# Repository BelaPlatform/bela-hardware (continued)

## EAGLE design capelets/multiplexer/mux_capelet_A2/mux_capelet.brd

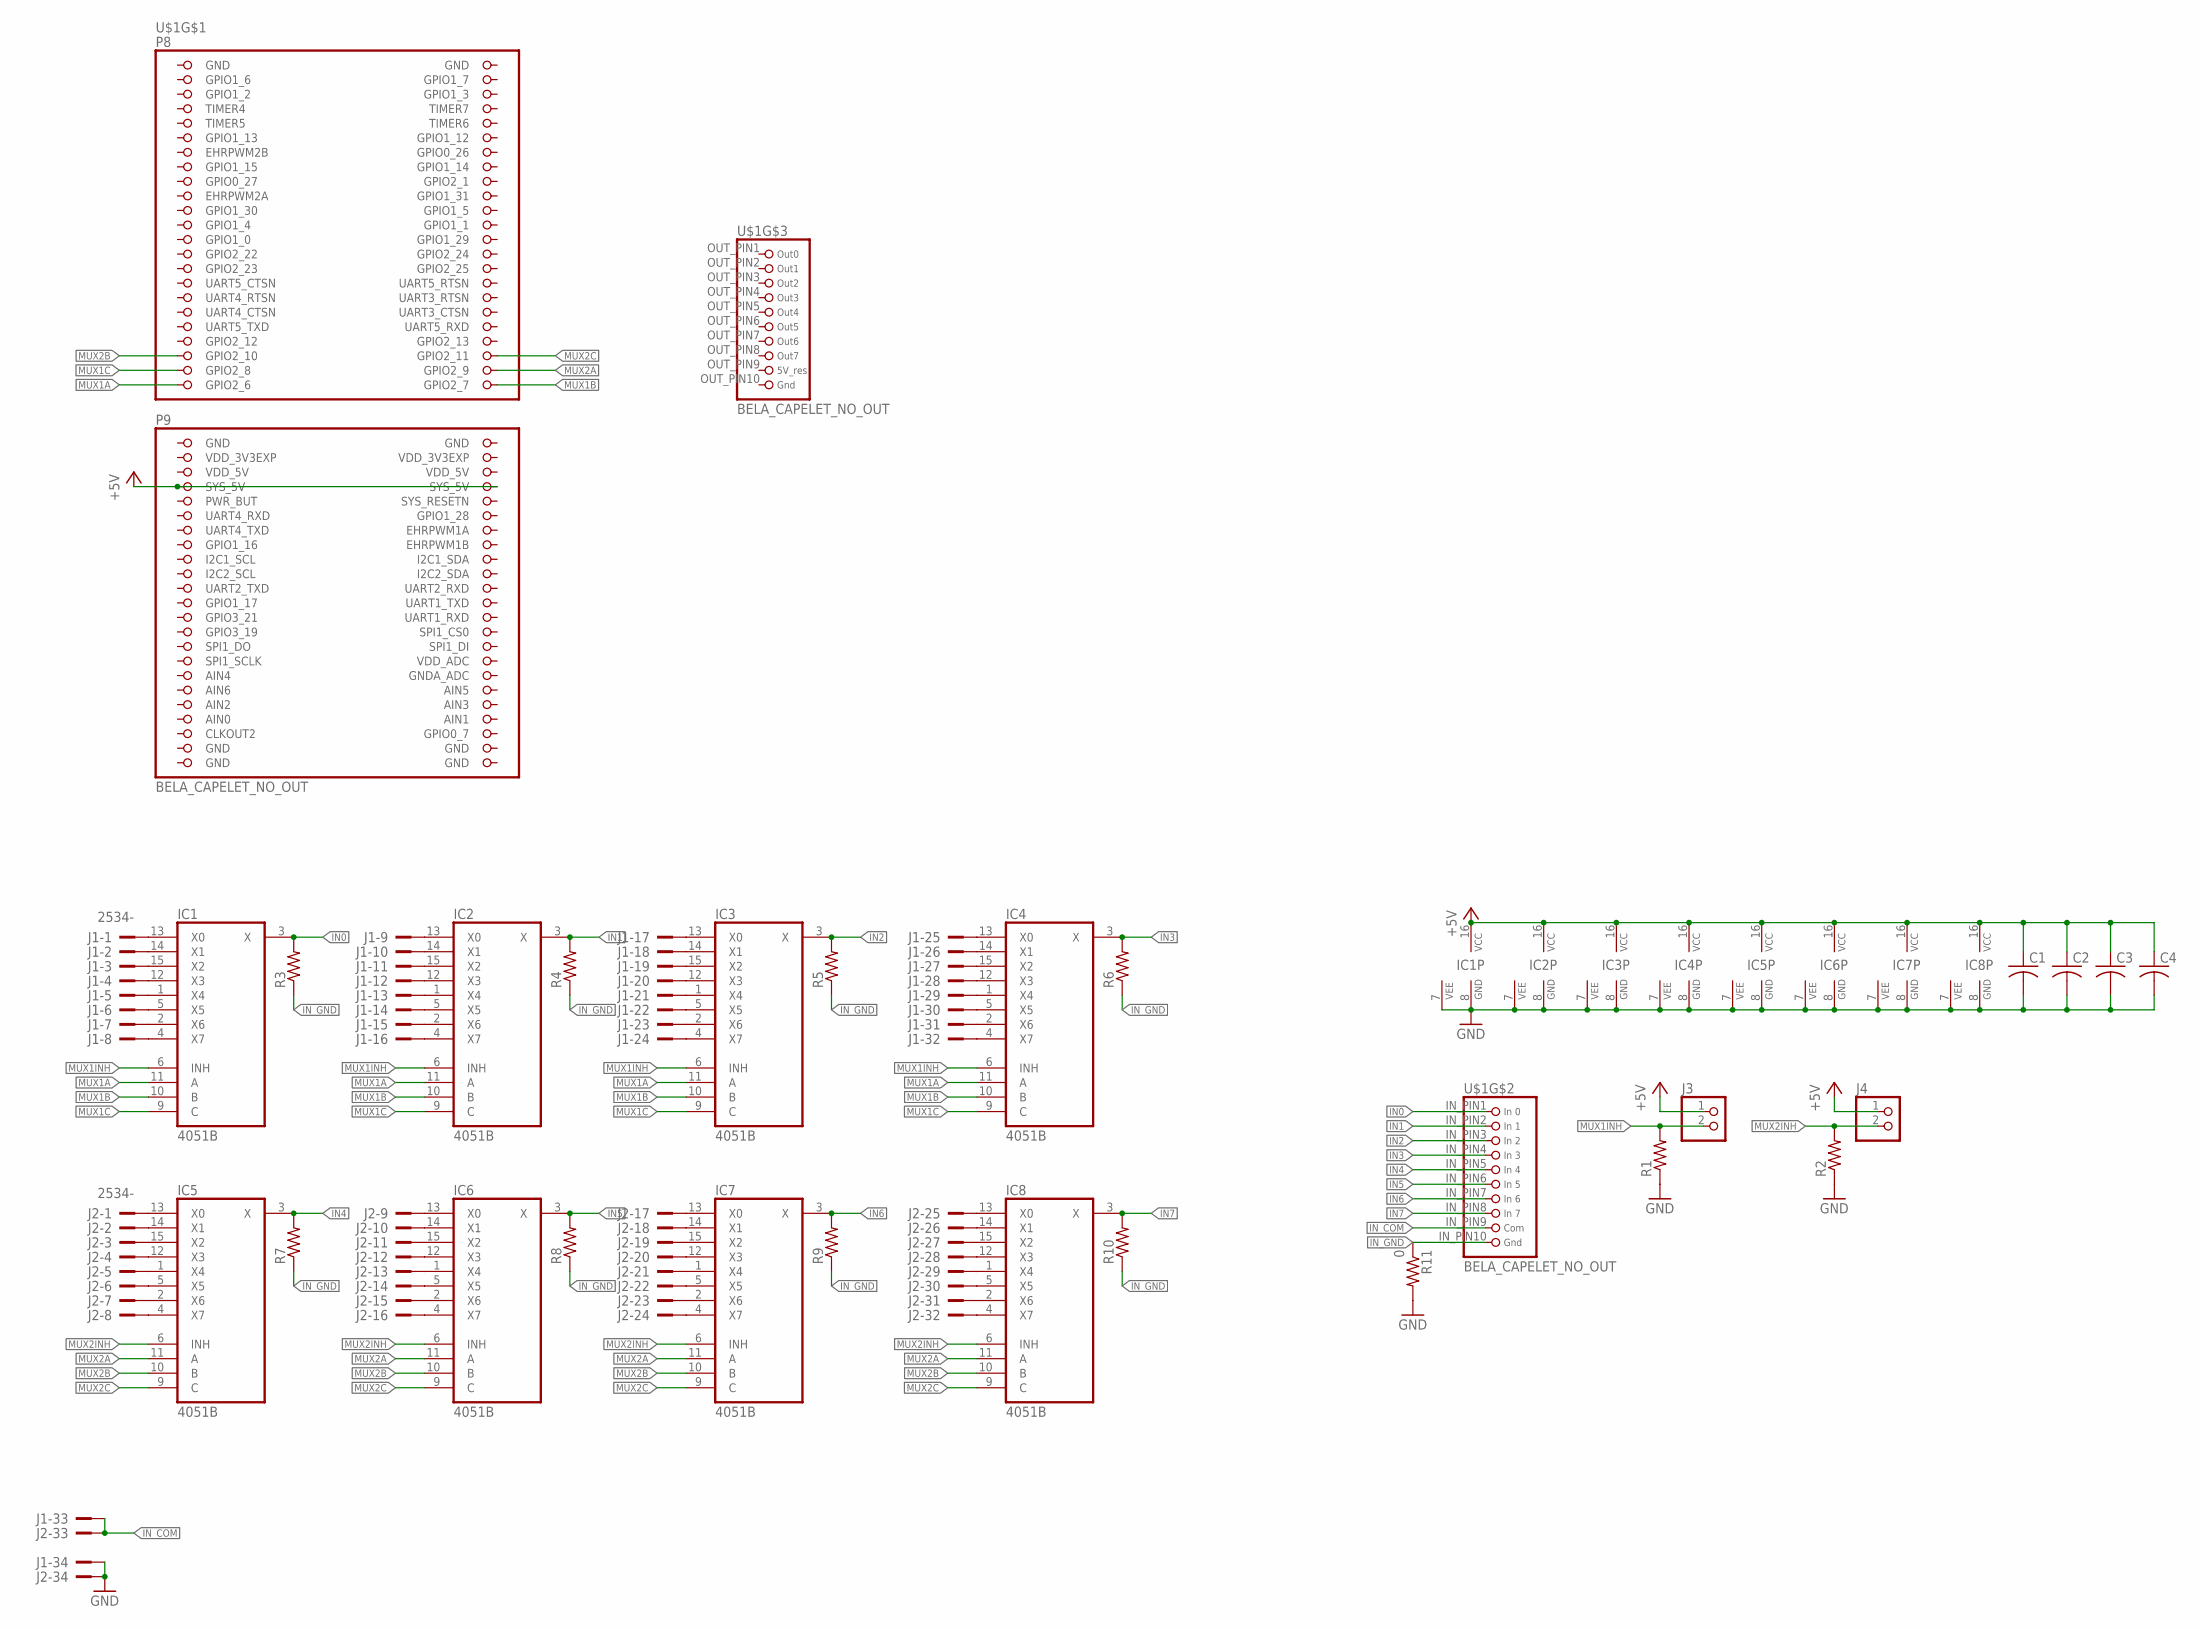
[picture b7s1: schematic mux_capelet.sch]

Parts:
C1, C2, C3, C4: C-USC0603; C0603
IC1, IC2, IC3, IC4, IC5, IC6, IC7, IC8: 4051B; TSSOP16-PW
J1, J2: 2534-; PAK100/2500-34
J3, J4: PINHD-1X2; 1X02
R1, R2, R3, R4, R5, R6, R7, R8, R9, R10: R-US_R0603; R0603
R11: 0; R0603
U$1: BELA_CAPELET_NO_OUT; BELA_CAPELET_NO_OUTLINE

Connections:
+5V: C1.1, C2.1, C3.1, C4.1, IC1.16 (VCC), IC2.16 (VCC), IC3.16 (VCC), IC4.16 (VCC), IC5.16 (VCC), IC6.16 (VCC), IC7.16 (VCC), IC8.16 (VCC), J3.1, J4.1, U$1.53 (SYS_5V), U$1.54 (SYS_5V)
AIN0: U$1.85 (AIN0)
GND: C1.2, C2.2, C3.2, C4.2, IC1.7 (VEE), IC1.8 (GND), IC2.7 (VEE), IC2.8 (GND), IC3.7 (VEE), IC3.8 (GND), IC4.7 (VEE), IC4.8 (GND), IC5.7 (VEE), IC5.8 (GND), IC6.7 (VEE), IC6.8 (GND), IC7.7 (VEE), IC7.8 (GND), IC8.7 (VEE), IC8.8 (GND), J1.34, J2.34, R1.1, R2.1, R11.2, U$1.1 (GND), U$1.2 (GND), U$1.47 (GND), U$1.48 (GND), U$1.89 (GND), U$1.90 (GND), U$1.91 (GND), U$1.92 (GND)
IN0: IC1.3 (X), R3.2, U$1.IN_PIN1 (1)
IN1: IC2.3 (X), R4.2, U$1.IN_PIN2 (2)
IN2: IC3.3 (X), R5.2, U$1.IN_PIN3 (3)
IN3: IC4.3 (X), R6.2, U$1.IN_PIN4 (4)
IN4: IC5.3 (X), R7.2, U$1.IN_PIN5 (5)
IN5: IC6.3 (X), R8.2, U$1.IN_PIN6 (6)
IN6: IC7.3 (X), R9.2, U$1.IN_PIN7 (7)
IN7: IC8.3 (X), R10.2, U$1.IN_PIN8 (8)
IN_COM: J1.33, J2.33, U$1.IN_PIN9 (9)
IN_GND: R3.1, R4.1, R5.1, R6.1, R7.1, R8.1, R9.1, R10.1, R11.1, U$1.IN_PIN10 (10)
J2: IC7.15 (X2), J2.19
MUX1A: IC1.11 (A), IC2.11 (A), IC3.11 (A), IC4.11 (A), U$1.45 (GPIO2_6)
MUX1B: IC1.10 (B), IC2.10 (B), IC3.10 (B), IC4.10 (B), U$1.46 (GPIO2_7)
MUX1C: IC1.9 (C), IC2.9 (C), IC3.9 (C), IC4.9 (C), U$1.43 (GPIO2_8)
MUX1INH: IC1.6 (INH), IC2.6 (INH), IC3.6 (INH), IC4.6 (INH), J3.2, R1.2
MUX2A: IC5.11 (A), IC6.11 (A), IC7.11 (A), IC8.11 (A), U$1.44 (GPIO2_9)
MUX2B: IC5.10 (B), IC6.10 (B), IC7.10 (B), IC8.10 (B), U$1.41 (GPIO2_10)
MUX2C: IC5.9 (C), IC6.9 (C), IC7.9 (C), IC8.9 (C), U$1.42 (GPIO2_11)
MUX2INH: IC5.6 (INH), IC6.6 (INH), IC7.6 (INH), IC8.6 (INH), J4.2, R2.2
unnamed: IC6.13 (X0), J2.9
unnamed: IC6.14 (X1), J2.10
unnamed: IC6.15 (X2), J2.11
unnamed: IC6.12 (X3), J2.12
unnamed: IC6.1 (X4), J2.13
unnamed: IC6.5 (X5), J2.14
unnamed: IC6.2 (X6), J2.15
unnamed: IC6.4 (X7), J2.16
unnamed: IC5.13 (X0), J2.1
unnamed: IC5.14 (X1), J2.2
unnamed: IC5.15 (X2), J2.3
unnamed: IC5.12 (X3), J2.4
unnamed: IC5.1 (X4), J2.5
unnamed: IC5.5 (X5), J2.6
unnamed: IC5.2 (X6), J2.7
unnamed: IC5.4 (X7), J2.8
unnamed: IC7.13 (X0), J2.17
unnamed: IC7.14 (X1), J2.18
unnamed: IC7.12 (X3), J2.20
unnamed: IC7.1 (X4), J2.21
unnamed: IC7.5 (X5), J2.22
unnamed: IC7.2 (X6), J2.23
unnamed: IC7.4 (X7), J2.24
unnamed: IC8.13 (X0), J2.25
unnamed: IC8.14 (X1), J2.26
unnamed: IC8.15 (X2), J2.27
unnamed: IC8.12 (X3), J2.28
unnamed: IC8.1 (X4), J2.29
unnamed: IC8.5 (X5), J2.30
unnamed: IC8.2 (X6), J2.31
unnamed: IC8.4 (X7), J2.32
unnamed: IC1.13 (X0), J1.1
unnamed: IC1.14 (X1), J1.2
unnamed: IC1.15 (X2), J1.3
unnamed: IC1.12 (X3), J1.4
unnamed: IC1.1 (X4), J1.5
unnamed: IC1.5 (X5), J1.6
unnamed: IC1.2 (X6), J1.7
unnamed: IC1.4 (X7), J1.8
unnamed: IC2.13 (X0), J1.9
unnamed: IC2.14 (X1), J1.10
unnamed: IC2.15 (X2), J1.11
unnamed: IC2.12 (X3), J1.12
unnamed: IC2.1 (X4), J1.13
unnamed: IC2.5 (X5), J1.14
unnamed: IC2.2 (X6), J1.15
unnamed: IC2.4 (X7), J1.16
unnamed: IC3.13 (X0), J1.17
unnamed: IC3.14 (X1), J1.18
unnamed: IC3.15 (X2), J1.19
unnamed: IC3.12 (X3), J1.20
unnamed: IC3.1 (X4), J1.21
unnamed: IC3.5 (X5), J1.22
unnamed: IC3.2 (X6), J1.23
unnamed: IC3.4 (X7), J1.24
unnamed: IC4.13 (X0), J1.25
unnamed: IC4.14 (X1), J1.26
unnamed: IC4.15 (X2), J1.27
unnamed: IC4.12 (X3), J1.28
unnamed: IC4.1 (X4), J1.29
unnamed: IC4.5 (X5), J1.30
unnamed: IC4.2 (X6), J1.31
unnamed: IC4.4 (X7), J1.32
VDD_3V3EXP: U$1.49 (VDD_3V3EXP), U$1.50 (VDD_3V3EXP)
VDD_5V: U$1.51 (VDD_5V), U$1.52 (VDD_5V)

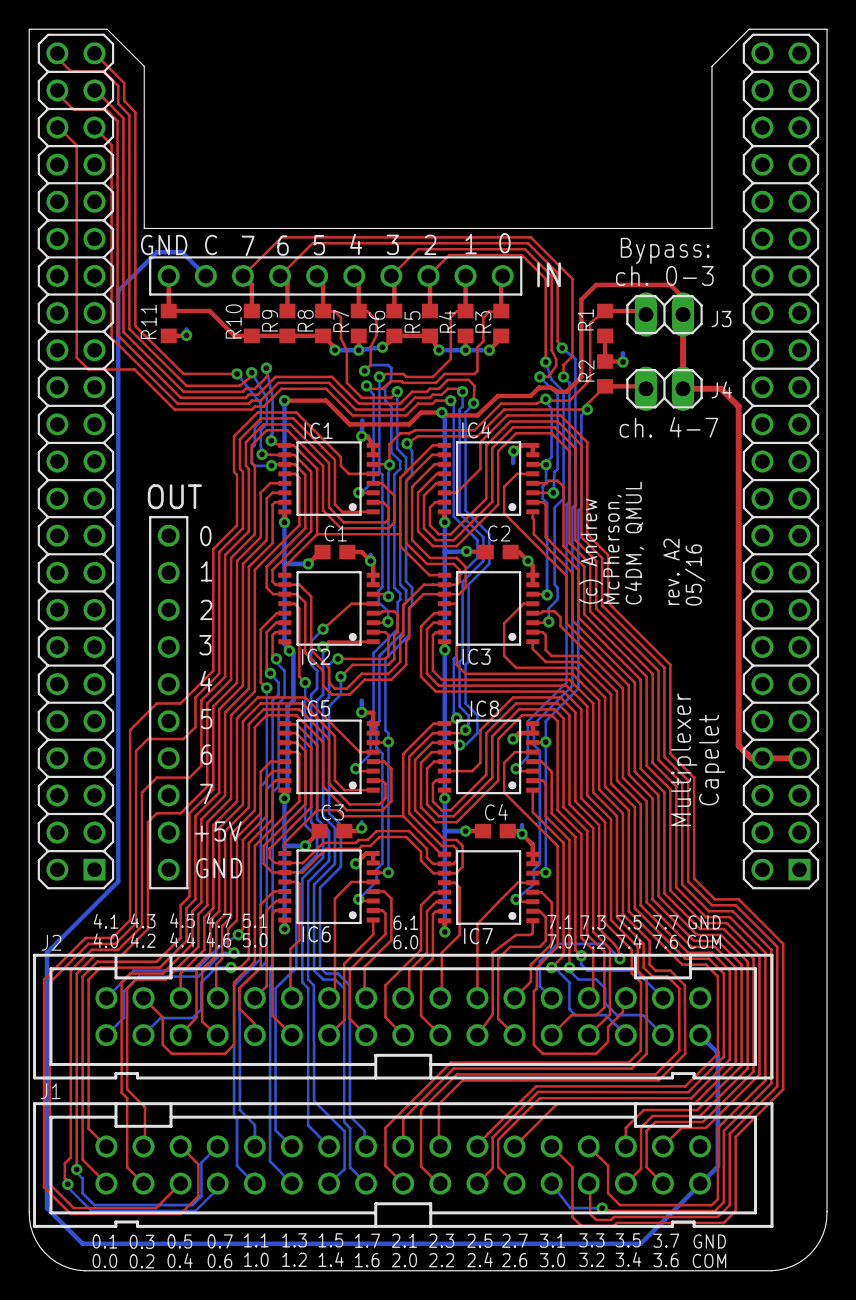
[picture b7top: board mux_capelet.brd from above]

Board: 2 copper layers, 54.6 x 85.0 mm, 28 parts (0 on the bottom side), 86 nets.

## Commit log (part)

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2016-07-22 Added Bela cape, multiplexer capelet and supporting EAGLE files
2016-07-26 Added Audio Expander Capelet design files (rev A2)
2016-10-10 Added pdf renders of the schematics
2016-12-08 Added pdf rendering of the board file for the cape
2017-05-18 Added frequency response for audio expander capelet
2017-09-01 Updated Bela cape to rev B2; closes #1, #2, #4
2017-09-25 Added PocketBela cape by @apmcpherson
2017-12-11 Added pdf rendering of the board and schematics for cape revB2
2018-01-23 Added rev. B mini cape files
2018-02-04 Updated Bela mini BOM to fix missing resistors and socket
2018-03-08 Added ESD suppressor IC6 to USB port; grounded USB ID pin; added labels and updated BOM
2018-03-11 Added Gerbers for mini cape rev. B2, updated BOM, and created an EAGLE CAM job for the mini cape.
2018-03-19 belamini test jig
2018-03-20 belamini test jig attempt 2
2018-03-20 Removed unneeded files
2018-03-20 Line out is DC-coupled, so no need for external components
2018-06-08 ignoring Eagle's temp files
2018-12-07 renamed belamini folder and added pdf schematics and board of belamini
2020-07-04 Added rev. B3 of the Bela cape
2020-07-04 Rev. B3 of the Bela Mini cape adds resistors R6 and R7 to reduce the noise when the audio output is driving a DI box and the codec is not active.
2020-07-04 Modified readme to also include Kicad as cad software used for the designs
2020-07-04 Updated with licensing details
2020-07-04 Added KiCad symbol and footprint for Bela Mini
2020-07-04 Add rev. B4 of Bela cape, moving some traces on the bottom layer for improved manufacturing reliability.
2020-11-30 Add manufacturing files for Bela Mini rev. B4
2020-11-30 Bela Mini rev. B4: addresses #7, #8, #10, #11
2021-11-09 Update README.md
    https://forum.kicad.info/t/warning-avoid-all-links-to-kicad-pcb-org-use-kicad-org/31521
2021-11-09 Update README.md (#13)
    https://forum.kicad.info/t/warning-avoid-all-links-to-kicad-pcb-org-use-kicad-org/31521
2022-01-11 MiniMulti rev. A2 designs
2022-03-24 Added dimensions pdf for Bela cape.
2022-03-24 Added dimensions pdf for bela mini starter kit
2022-08-16 First draft of mini rev. C1, with new ADC and move to KiCad
2022-08-16 Added Bela Mini rev. C2, fixing a couple issues in C1
2022-08-16 Mini rev. C1: change IC3 on the BOM
2022-08-16 Add logo to Mini rev. C1, clean up schematic and add production files
2023-01-05 typo
2023-03-12 ignore backup files since we have git history, right?
2023-03-12 updated gitignore
2023-03-12 Updates to Bela cape C1, adding 3-pin connectors for raw analog out
    (cherry picked from commit eb88a9ebe73bf9c3f735ce6d0fd609408781e91a)
2023-03-12 Bela cape rev. C1 - design in progress
    (cherry picked from commit 96cf0ad517c32be44510b9f78b20fff38d2effcd)
2023-03-12 More C1 cape routing
    (cherry picked from commit db7d999e21b46c22925661ce0002776775f31ffd)
2023-03-12 Further routing on C1 cape
    (cherry picked from commit 232a25b01e013bf194cdc3a343766aa7b43870aa)
2023-03-12 First complete routing of C1 cape
    (cherry picked from commit 8c5092941a0b3ec42f55098733fd0108b2086674)
2023-03-12 C1 cape: clean up bottom silkscreen
    (cherry picked from commit 7c02b20f8f7a862246e5856b6fa8015b8ad6464b)
2023-03-12 Ignored (and discarded) kicad_prl files
    (cherry picked from commit b86f11e499d9a74027bf78e27e7b6f224d72f43f)
2023-03-12 Further C1 cape updates
    (cherry picked from commit 4c76e949636c5b1483c5ffba2ecc0f217292ab87)
2023-03-12 Bela cape C1: renumber components
    (cherry picked from commit 6ebfe9c44bb7559ffb4c9dbd092e49803523e6a1)
2023-03-12 First complete iteration of C1 cape layout
    (cherry picked from commit 0ee733c70b42f416809330055e007cefcdb105fa)
2023-03-12 changed board setup to include Bela cape colors, added 3dmodels for button and LED
    (cherry picked from commit fac969fb978c1abdbab94b44e3f4f5c1f13dcd93)
2023-03-12 Bela cape rev. C2
    (cherry picked from commit 085b3700cd1d9a25c77092a8b59a7c103f45927b)
2023-03-12 added missing 3dmodels for IC packages
    (cherry picked from commit 85806714f40e67aeb9d357d275771518137d9dca)
2023-03-12 Bodge board to fix an error on C2 capes
    (cherry picked from commit f68d599e191e370001d2d3aca018898c47946fe5)
2023-03-12 added NC flags to pins in Cape rev C2 to reduce ERC errors
    (cherry picked from commit 3da46686a35f9c5723f0363d277e8b6402ee2362)
2023-03-12 Changed panel to 6x7 with 3mm gap and 0.35mm distance to v-scoring.
    (cherry picked from commit ada2b1bb84732b3d844c1010702f27f798faad04)
2023-03-12 A few edits to C2 cape
    (cherry picked from commit 42570a0d57f5cd6d8ff56c36d77f2d0b211cc62f)
2023-03-12 Edit to C2 cape fix
    (cherry picked from commit b205a86061b78b52253ac275e5139adb0c372d47)
2023-03-12 Added kikit configuration file for posterity
    (cherry picked from commit 343436336812e16e1a1f06097494a23a2ce2b96c)
2023-03-12 Added panel and gerbers for fix board
    (cherry picked from commit a0c660b927de1cd35729b3ca257c25d34b100ddd)
2023-03-12 Cape rev C3 first draft
    (cherry picked from commit 13e247bb11a8ca90d5cea0bc35d4eceea4ae0f39)
2023-03-12 Reduce size of connector holes on C3 cape
    (cherry picked from commit 2d14684a246b05362e5486009cff8026d4af1add)
2023-03-12 Add analog out connection to P8.15 for future BBAI64 support
2024-02-27 removed sym-lib-table with a reference to an unused and obsolete local library
2024-02-27 added missing footprints and symbols, updated their use in the schematic, referenced them as local path in schematic and layout
2024-12-06 Adding bela mini add-on footprint
2025-04-11 Added belamini system 3dmodel, updated footprint
2025-04-16 added audio I/O to belamini symbol/fp, made footprint DRC error-free
2026-02-06 Added Bela-Gem symbols, footprints, 3d
2026-02-06 added GemStereo and GemMulti A4
2026-02-07 adding spacers, screw, PB2 models
2026-02-09 removed logos
2026-02-13 Renaming Gem KiCad files
2026-03-19 bela-kicad-library updated to 6883fdbc30aeec6c245b02afa28c44308841621c
2026-05-04 adding VIN (P1.1) to standard Gem Stereo/Multi Symbols/
2026-05-22 added GemMulti wing_top and wing_bottom from a7cc44841b7c9501ee3d858750621b35dcaec8b8
